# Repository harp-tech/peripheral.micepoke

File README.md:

# Peripheral - Mice Poke

## General description

----

[//]: # (Tables can be generated using: https://www.tablesgenerator.com/markdown_tables)

## Hardware compatibility

| Peripheral HW Version 	| Board           	                                                | Board HW Version 	| Notes                            	|
|-----------------------	|-----------------	                                                |------------------	|----------------------------------	|
| **1.3**                 | [Device.Behavior](https://github.com/harp-tech/device.behavior) 	| > 1.0             |                                	|
| **1.2**                 | [Device.Behavior](https://github.com/harp-tech/device.behavior)   | > 1.0             |                                	|
|                       	|                 	                                                |                  	|                                  	|
----

## Key Features

* Poke detection through an infrared beam
* Control of 2 LEDs + an external LED
* 12V valve control when connected to an Harp Behavior

----

## Connectivity [v1.3]

* 1x 12V Valve [screw terminal]  
* 1x DIO, IR LED, IR Photodiode, LED, 5V, GND  [screw terminal] 

----

## Licensing

License files can be found, and are applied to, each individual subfolder in this repository.

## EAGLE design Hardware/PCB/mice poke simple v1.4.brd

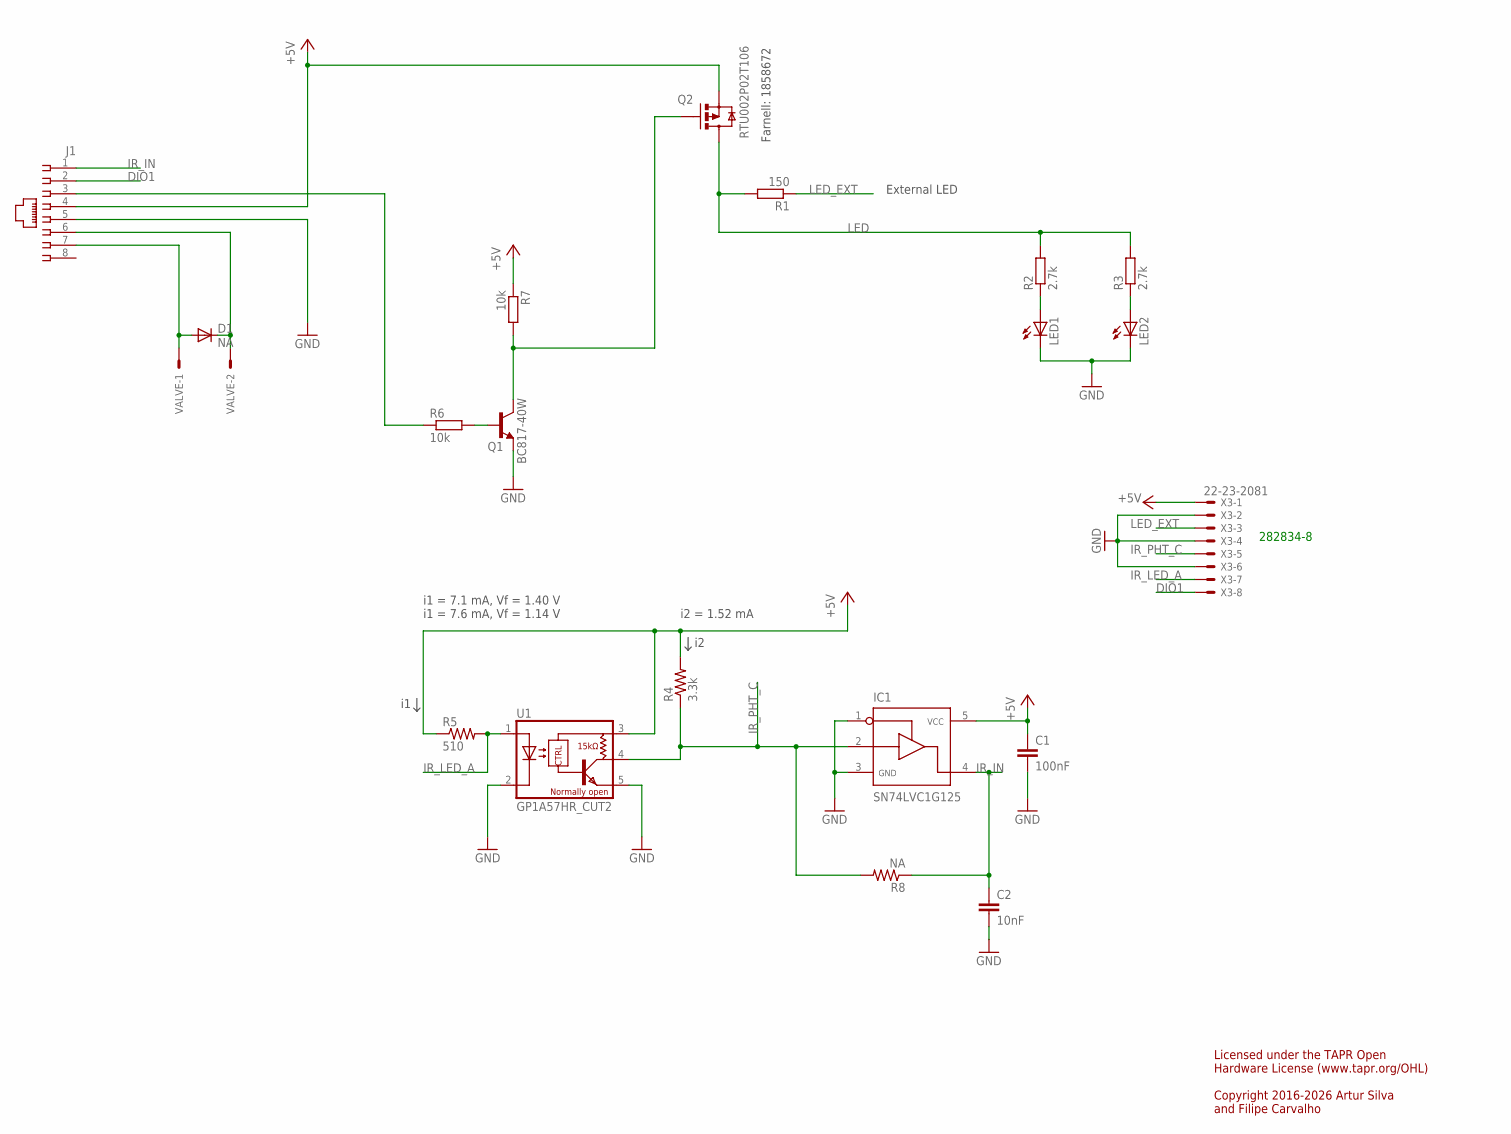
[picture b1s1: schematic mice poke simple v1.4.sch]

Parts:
C1: 100nF; C0402
C2: 10nF; C0402
D1: NA; SOD323-R
IC1: SN74LVC1G125; SOT23-5
J1: 215878-2
LED1, LED2: LED3MM
Q1: BC817-40W; SOT323-BEC
Q2: RTU002P02T106; SOT323
R1: 150; R0402
R2, R3: 2.7k; R0402
R4: 3.3k; R0402
R5: 510; R0402
R6, R7: 10k; R0402
R8: NA; R0402
U1: GP1A57HR_CUT2
VALVE: 22-23-2021
X3: 22-23-2081

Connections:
+5V: C1.1, IC1.5, J1.4, Q2.1 (S), R4.2, R5.1, R7.1, U1.3 (VCC), X3.1
DIO1: J1.2, X3.8
GND: C1.2, C2.2, IC1.1, IC1.3, J1.5, LED1.K (C), LED2.K (C), Q1.E, U1.2 (C), U1.5 (GND), X3.2, X3.4, X3.6
IR_IN: C2.1, IC1.4, J1.1, R8.1
IR_LED_A: R5.2, U1.1 (A), X3.7
IR_PHT_C: IC1.2, R4.1, R8.2, U1.4 (VO), X3.5
LED: Q2.3 (D), R1.2, R2.2, R3.2
LED_EXT: R1.1, X3.3
unnamed: D1.A, J1.7, VALVE.1
unnamed: D1.C, J1.6, VALVE.2
unnamed: J1.3, R6.1
unnamed: LED2.A, R3.1
unnamed: LED1.A, R2.1
unnamed: Q1.C, Q2.2 (G), R7.2
unnamed: Q1.B, R6.2

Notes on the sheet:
i1 = 7.1 mA, Vf = 1.40 V i1 = 7.6 mA, Vf = 1.14 V
i2 = 1.52 mA
External LED
Farnell: 1858672
Licensed under the TAPR Open Hardware License (www.tapr.org/OHL) Copyright 2016-2026 Artur Silva and Filipe Carvalho
282834-8

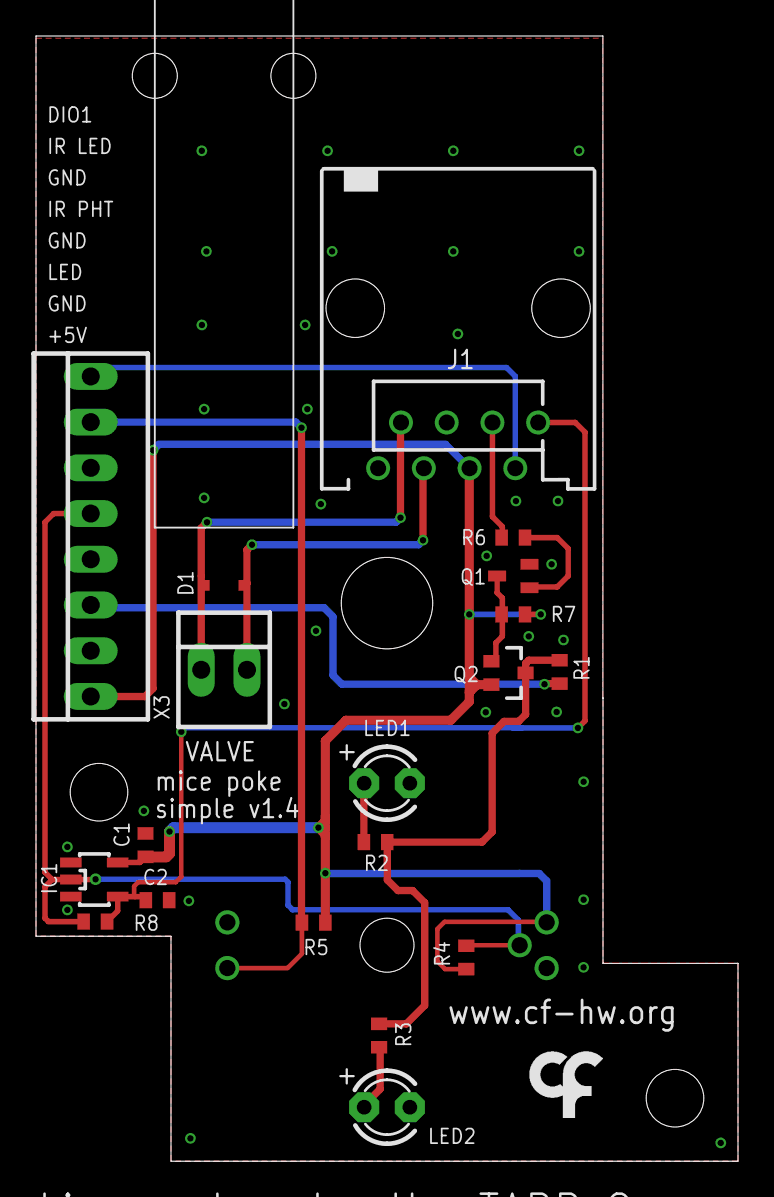
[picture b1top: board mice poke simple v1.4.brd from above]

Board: 2 copper layers, 39.0 x 62.5 mm, 21 parts (1 on the bottom side), 15 nets.

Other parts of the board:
U$2: LOGO_7

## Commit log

2022-09-16 Organize folders and add peripheral boards
2022-09-16 License files added
2022-12-13 Move design files to PCB folder
2022-12-13 Change folder name
2022-12-13 Update placeholder README
2022-12-15 Move PCB license to subfolder
2022-12-23 refactor repository structure
2023-11-01 add license file to mechanical
2023-11-01 Update readme file
2023-11-01 Add pcb image
2023-11-01 Remove license extensions
2024-01-29 add STEP files for pokes
2024-05-23 Add poke version 1.3
2026-04-24 Updated valve footprint and increased resistors.
